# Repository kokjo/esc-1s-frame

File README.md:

FPV Drone ESC, With PCB as FRAME
================================

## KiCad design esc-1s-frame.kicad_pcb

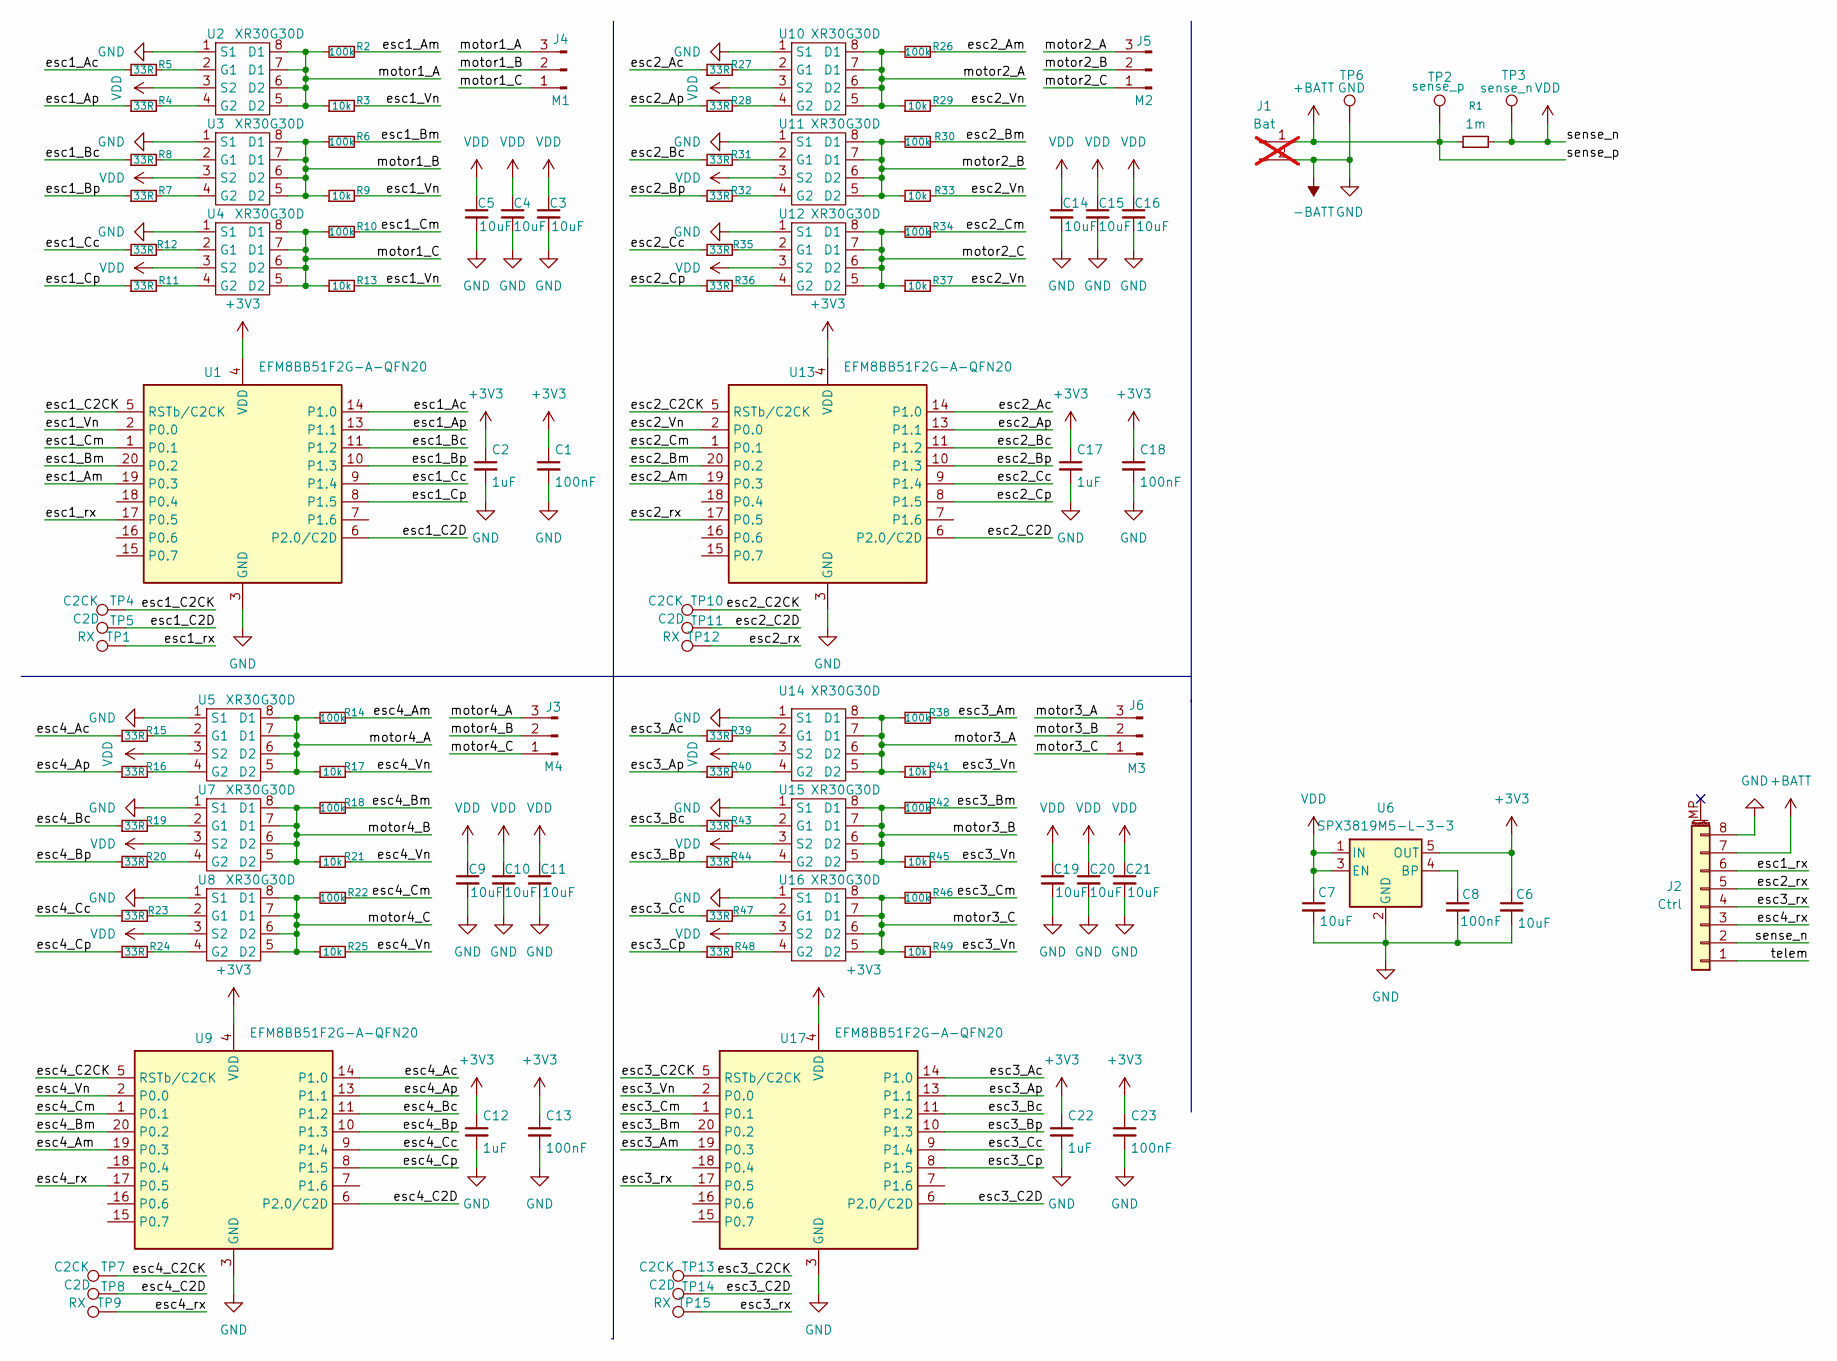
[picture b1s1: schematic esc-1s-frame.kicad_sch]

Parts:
C1, C8, C13, C18, C23: 100nF; C_0402_1005Metric
C2, C12, C17, C22: 1uF; C_0402_1005Metric
C3, C4, C5, C6, C7, C9, C10, C11, C14, C15, C16, C19, C20, C21: 10uF; C_0805_2012Metric
J1: Bat; PinHeader_1x02_P2.54mm_Vertical; not fitted
J2: Ctrl; JST_SH_SM08B-SRSS-TB_1x08-1MP_P1.00mm_Horizontal
J3: M4; Molex_PicoBlade_53048-0310_1x03_P1.25mm_Horizontal
J4: M1; Molex_PicoBlade_53048-0310_1x03_P1.25mm_Horizontal
J5: M2; Molex_PicoBlade_53048-0310_1x03_P1.25mm_Horizontal
J6: M3; Molex_PicoBlade_53048-0310_1x03_P1.25mm_Horizontal
R1: 1m; R_0805_2012Metric_Pad1.20x1.40mm_HandSolder
R2, R6, R10, R14, R18, R22, R26, R30, R34, R38, R42, R46: 100k; R_0402_1005Metric
R3, R9, R13, R17, R21, R25, R29, R33, R37, R41, R45, R49: 10k; R_0402_1005Metric
R4, R5, R7, R8, R11, R12, R15, R16, R19, R20, R23, R24, R27, R28, R31, R32, R35, R36, R39, R40, R43, R44, R47, R48: 33R; R_0402_1005Metric
TP1, TP9, TP12, TP15: RX; TestPoint_Pad_D1.0mm
TP2: sense_p; TestPoint_Pad_D1.0mm
TP3: sense_n; TestPoint_Pad_D1.0mm
TP4, TP7, TP10, TP13: C2CK; TestPoint_Pad_D1.0mm
TP5, TP8, TP11, TP14: C2D; TestPoint_Pad_D1.0mm
TP6: GND; TestPoint_Pad_1.0x1.0mm
U1, U9, U13, U17: EFM8BB51F2G-A-QFN20; SiliconLabs_QFN-20-1EP_3x3mm_P0.5mm_EP1.8x1.8mm
U2, U3, U4, U5, U7, U8, U10, U11, U12, U14, U15, U16: XR30G30D; DFN-8-1EP_3x3mm_P0.65mm_EP1.55x2.4mm
U6: SPX3819M5-L-3-3; SOT-23-5

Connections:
+3V3: C1.1, C2.1, C6.1, C12.1, C13.1, C17.1, C18.1, C22.1, C23.1, U1.4 (VDD), U6.5 (OUT), U9.4 (VDD), U13.4 (VDD), U17.4 (VDD)
+BATT: J1.1, J2.7, R1.1, TP2.1
-BATT: C1.2, C2.2, C3.2, C4.2, C5.2, C6.2, C7.2, C8.2, C9.2, C10.2, C11.2, C12.2, C13.2, C14.2, C15.2, C16.2, C17.2, C18.2, C19.2, C20.2, C21.2, C22.2, C23.2, J1.2, J2.8, TP6.1, U1.3 (GND), U1.12 (GND), U1.21 (GND), U2.1 (S1), U3.1 (S1), U4.1 (S1), U5.1 (S1), U6.2 (GND), U7.1 (S1), U8.1 (S1), U9.3 (GND), U9.12 (GND), U9.21 (GND), U10.1 (S1), U11.1 (S1), U12.1 (S1), U13.3 (GND), U13.12 (GND), U13.21 (GND), U14.1 (S1), U15.1 (S1), U16.1 (S1), U17.3 (GND), U17.12 (GND), U17.21 (GND)
/esc1_Ac: R5.1, U1.14 (P1.0)
/esc1_Am: R2.1, U1.19 (P0.3)
/esc1_Ap: R4.1, U1.13 (P1.1)
/esc1_Bc: R8.1, U1.11 (P1.2)
/esc1_Bm: R6.1, U1.20 (P0.2)
/esc1_Bp: R7.1, U1.10 (P1.3)
/esc1_C2CK: TP4.1, U1.5 (RSTb/C2CK)
/esc1_C2D: TP5.1, U1.6 (P2.0/C2D)
/esc1_Cc: R12.1, U1.9 (P1.4)
/esc1_Cm: R10.1, U1.1 (P0.1)
/esc1_Cp: R11.1, U1.8 (P1.5)
/esc1_Vn: R3.2, R9.2, R13.2, U1.2 (P0.0)
/esc1_rx: J2.6, TP1.1, U1.17 (P0.5)
/esc2_Ac: R27.1, U13.14 (P1.0)
/esc2_Am: R26.1, U13.19 (P0.3)
/esc2_Ap: R28.1, U13.13 (P1.1)
/esc2_Bc: R31.1, U13.11 (P1.2)
/esc2_Bm: R30.1, U13.20 (P0.2)
/esc2_Bp: R32.1, U13.10 (P1.3)
/esc2_C2CK: TP10.1, U13.5 (RSTb/C2CK)
/esc2_C2D: TP11.1, U13.6 (P2.0/C2D)
/esc2_Cc: R35.1, U13.9 (P1.4)
/esc2_Cm: R34.1, U13.1 (P0.1)
/esc2_Cp: R36.1, U13.8 (P1.5)
/esc2_Vn: R29.2, R33.2, R37.2, U13.2 (P0.0)
/esc2_rx: J2.5, TP12.1, U13.17 (P0.5)
/esc3_Ac: R39.1, U17.14 (P1.0)
/esc3_Am: R38.1, U17.19 (P0.3)
/esc3_Ap: R40.1, U17.13 (P1.1)
/esc3_Bc: R43.1, U17.11 (P1.2)
/esc3_Bm: R42.1, U17.20 (P0.2)
/esc3_Bp: R44.1, U17.10 (P1.3)
/esc3_C2CK: TP13.1, U17.5 (RSTb/C2CK)
/esc3_C2D: TP14.1, U17.6 (P2.0/C2D)
/esc3_Cc: R47.1, U17.9 (P1.4)
/esc3_Cm: R46.1, U17.1 (P0.1)
/esc3_Cp: R48.1, U17.8 (P1.5)
/esc3_Vn: R41.2, R45.2, R49.2, U17.2 (P0.0)
/esc3_rx: J2.4, TP15.1, U17.17 (P0.5)
/esc4_Ac: R15.1, U9.14 (P1.0)
/esc4_Am: R14.1, U9.19 (P0.3)
/esc4_Ap: R16.1, U9.13 (P1.1)
/esc4_Bc: R19.1, U9.11 (P1.2)
/esc4_Bm: R18.1, U9.20 (P0.2)
/esc4_Bp: R20.1, U9.10 (P1.3)
/esc4_C2CK: TP7.1, U9.5 (RSTb/C2CK)
/esc4_C2D: TP8.1, U9.6 (P2.0/C2D)
/esc4_Cc: R23.1, U9.9 (P1.4)
/esc4_Cm: R22.1, U9.1 (P0.1)
/esc4_Cp: R24.1, U9.8 (P1.5)
/esc4_Vn: R17.2, R21.2, R25.2, U9.2 (P0.0)
/esc4_rx: J2.3, TP9.1, U9.17 (P0.5)
/motor1_A: J4.3, R2.2, R3.1, U2.5 (D2), U2.6 (D2), U2.7 (D1), U2.8 (D1)
/motor1_B: J4.2, R6.2, R9.1, U3.5 (D2), U3.6 (D2), U3.7 (D1), U3.8 (D1)
/motor1_C: J4.1, R10.2, R13.1, U4.5 (D2), U4.6 (D2), U4.7 (D1), U4.8 (D1)
/motor2_A: J5.3, R26.2, R29.1, U10.5 (D2), U10.6 (D2), U10.7 (D1), U10.8 (D1)
/motor2_B: J5.2, R30.2, R33.1, U11.5 (D2), U11.6 (D2), U11.7 (D1), U11.8 (D1)
/motor2_C: J5.1, R34.2, R37.1, U12.5 (D2), U12.6 (D2), U12.7 (D1), U12.8 (D1)
/motor3_A: J6.3, R38.2, R41.1, U14.5 (D2), U14.6 (D2), U14.7 (D1), U14.8 (D1)
/motor3_B: J6.2, R42.2, R45.1, U15.5 (D2), U15.6 (D2), U15.7 (D1), U15.8 (D1)
/motor3_C: J6.1, R46.2, R49.1, U16.5 (D2), U16.6 (D2), U16.7 (D1), U16.8 (D1)
/motor4_A: J3.3, R14.2, R17.1, U5.5 (D2), U5.6 (D2), U5.7 (D1), U5.8 (D1)
/motor4_B: J3.2, R18.2, R21.1, U7.5 (D2), U7.6 (D2), U7.7 (D1), U7.8 (D1)
/motor4_C: J3.1, R22.2, R25.1, U8.5 (D2), U8.6 (D2), U8.7 (D1), U8.8 (D1)
/telem: J2.1
unnamed: R5.2, U2.2 (G1)
unnamed: R4.2, U2.4 (G2)
unnamed: R8.2, U3.2 (G1)
unnamed: R7.2, U3.4 (G2)
unnamed: R12.2, U4.2 (G1)
unnamed: R11.2, U4.4 (G2)
unnamed: R15.2, U5.2 (G1)
unnamed: R16.2, U5.4 (G2)
unnamed: C8.1, U6.4 (BP)
unnamed: R19.2, U7.2 (G1)
unnamed: R20.2, U7.4 (G2)
unnamed: R23.2, U8.2 (G1)
unnamed: R24.2, U8.4 (G2)
unnamed: R27.2, U10.2 (G1)
unnamed: R28.2, U10.4 (G2)
unnamed: R31.2, U11.2 (G1)
unnamed: R32.2, U11.4 (G2)
unnamed: R35.2, U12.2 (G1)
unnamed: R36.2, U12.4 (G2)
unnamed: R39.2, U14.2 (G1)
unnamed: R40.2, U14.4 (G2)
unnamed: R43.2, U15.2 (G1)
unnamed: R44.2, U15.4 (G2)
unnamed: R47.2, U16.2 (G1)
unnamed: R48.2, U16.4 (G2)
VDD: C3.1, C4.1, C5.1, C7.1, C9.1, C10.1, C11.1, C14.1, C15.1, C16.1, C19.1, C20.1, C21.1, J2.2, R1.2, TP3.1, U2.3 (S2), U3.3 (S2), U4.3 (S2), U5.3 (S2), U6.1 (IN), U6.3 (EN), U7.3 (S2), U8.3 (S2), U10.3 (S2), U11.3 (S2), U12.3 (S2), U14.3 (S2), U15.3 (S2), U16.3 (S2)

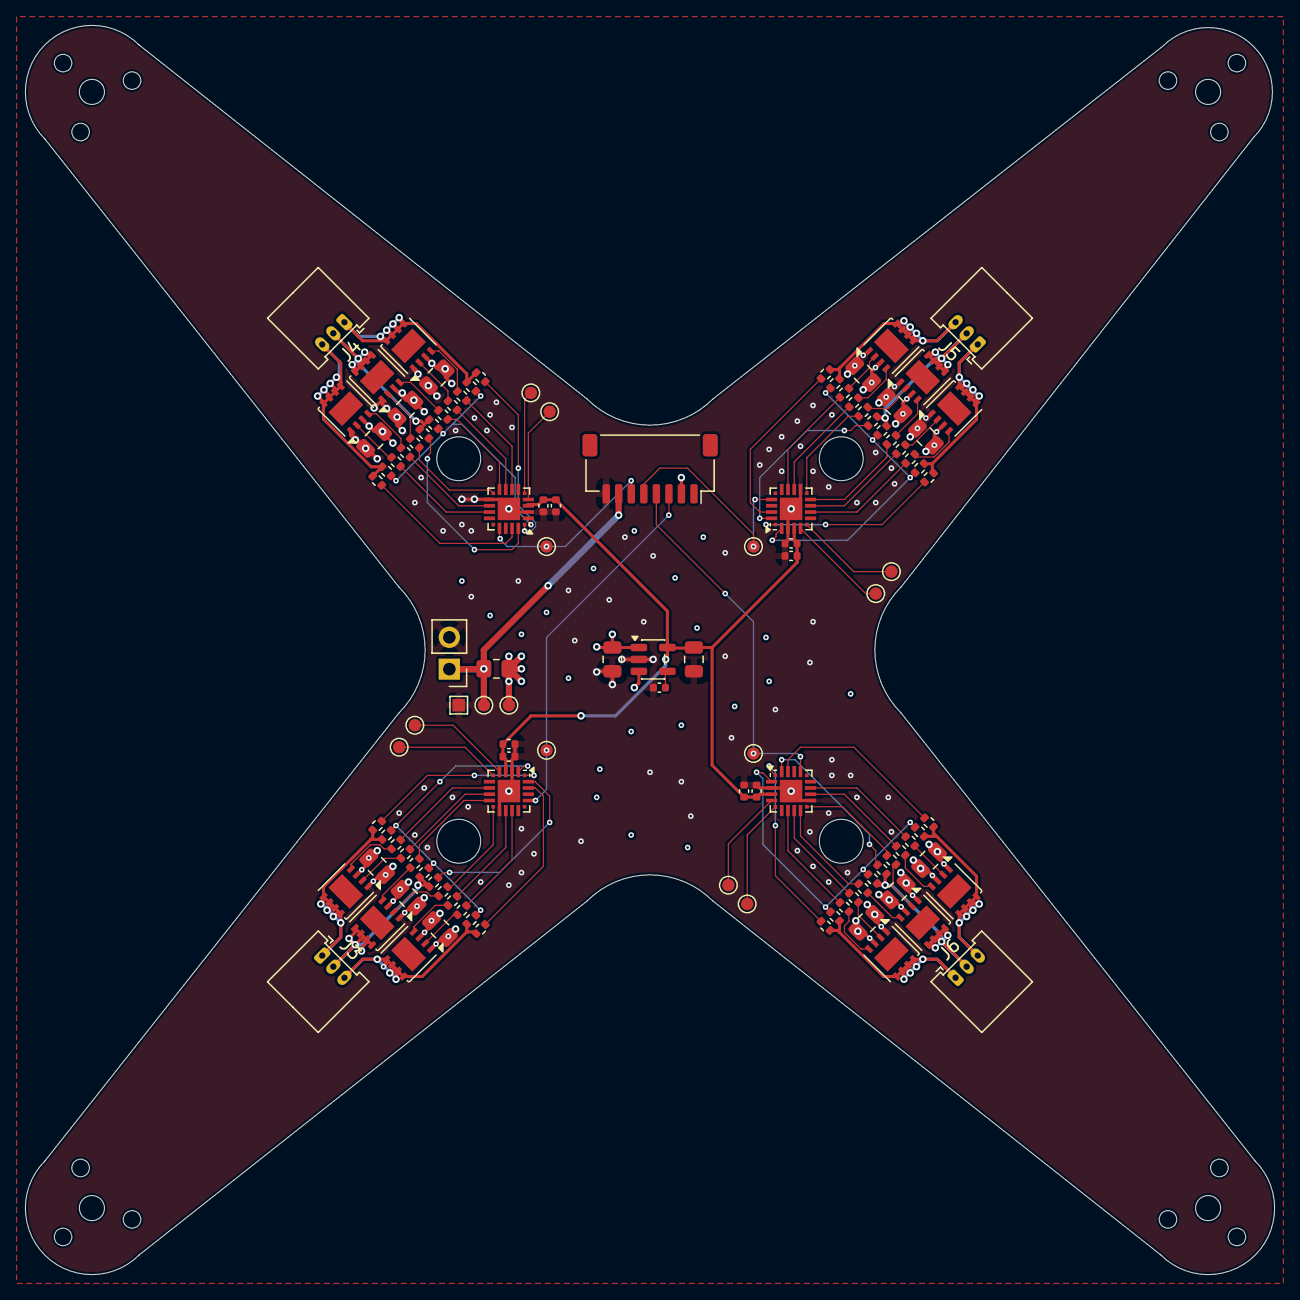
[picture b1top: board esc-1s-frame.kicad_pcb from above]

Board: 4 copper layers, 99.6 x 99.6 mm, 110 parts (0 on the bottom side), 93 nets.

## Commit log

2026-06-02 sent to jlcpcb
2026-06-09 full board, sent to jlcpcb
2026-06-09 Add README.md
